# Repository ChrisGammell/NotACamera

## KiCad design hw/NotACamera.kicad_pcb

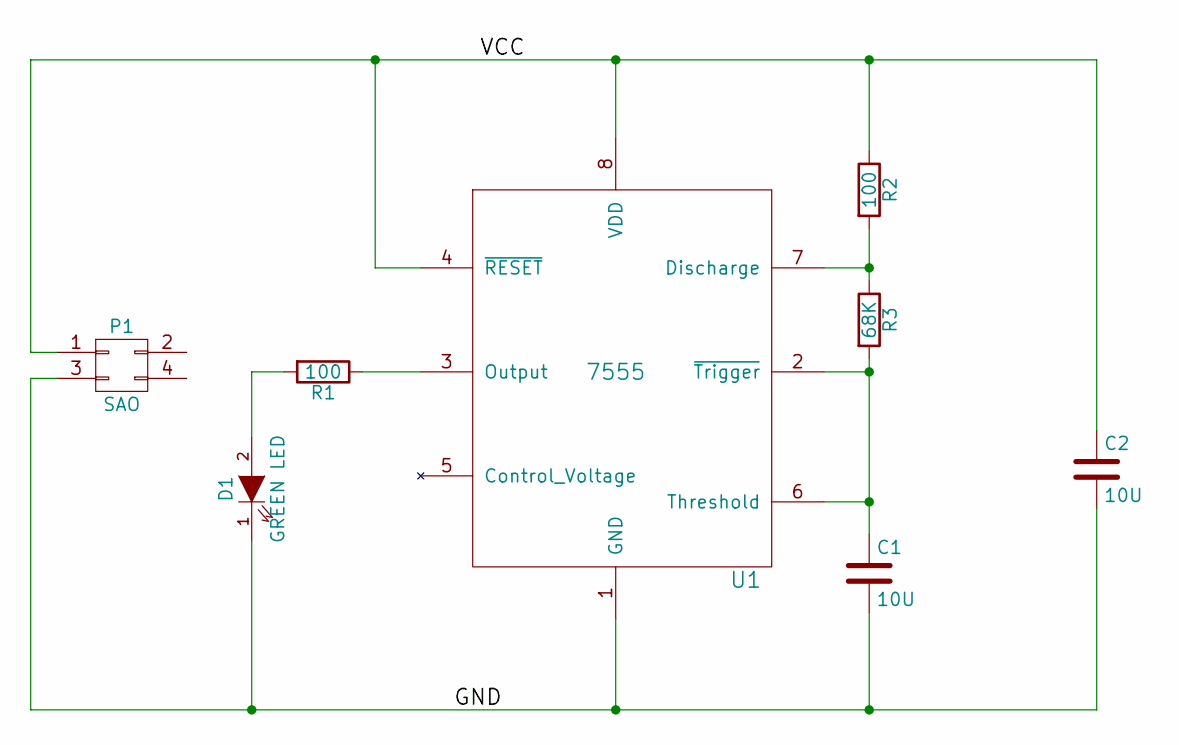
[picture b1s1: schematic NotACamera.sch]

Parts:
C1, C2: 10U; R_0805_HandSoldering; MPN MPN
D1: GREEN LED; R_0805_HandSoldering; MPN MPN
P1: SAO; Pin_Header_Straight_2x02
R1, R2: 100; R_0805_HandSoldering; MPN MPN
R3: 68K; R_0805_HandSoldering; MPN MPN
U1: 7555; SOIC-8-N

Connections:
/GND: C1.2, C2.2, D1.1 (K), P1.3, U1.1 (GND)
/VCC: C2.1, P1.1, R2.1, U1.4 (~RESET), U1.8 (VDD)
unnamed: C1.1, R3.2, U1.2 (~Trigger), U1.6 (Threshold)
unnamed: D1.2 (A), R1.2
unnamed: R1.1, U1.3 (Output)
unnamed: R2.2, R3.1, U1.7 (Discharge)

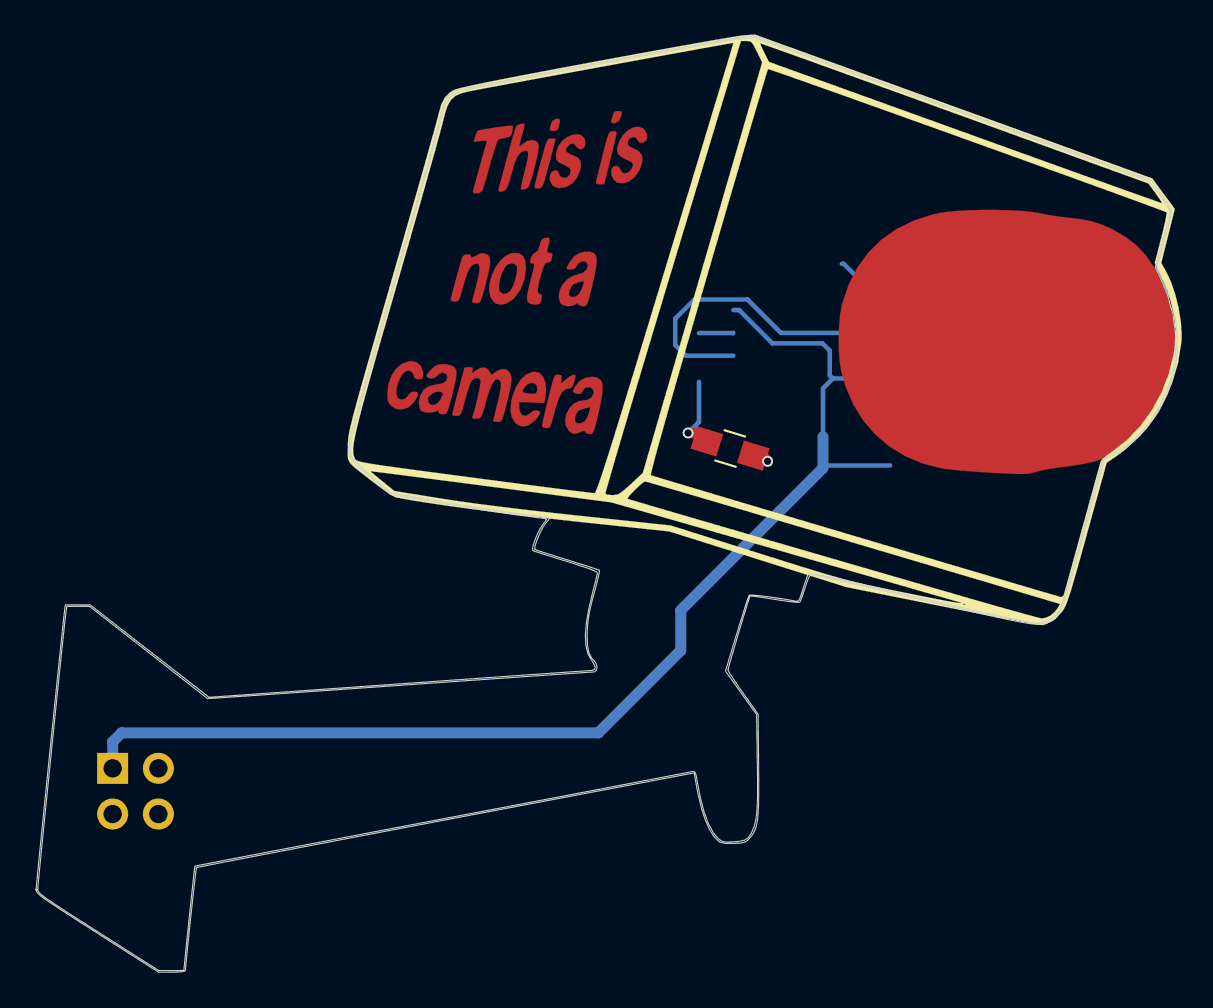
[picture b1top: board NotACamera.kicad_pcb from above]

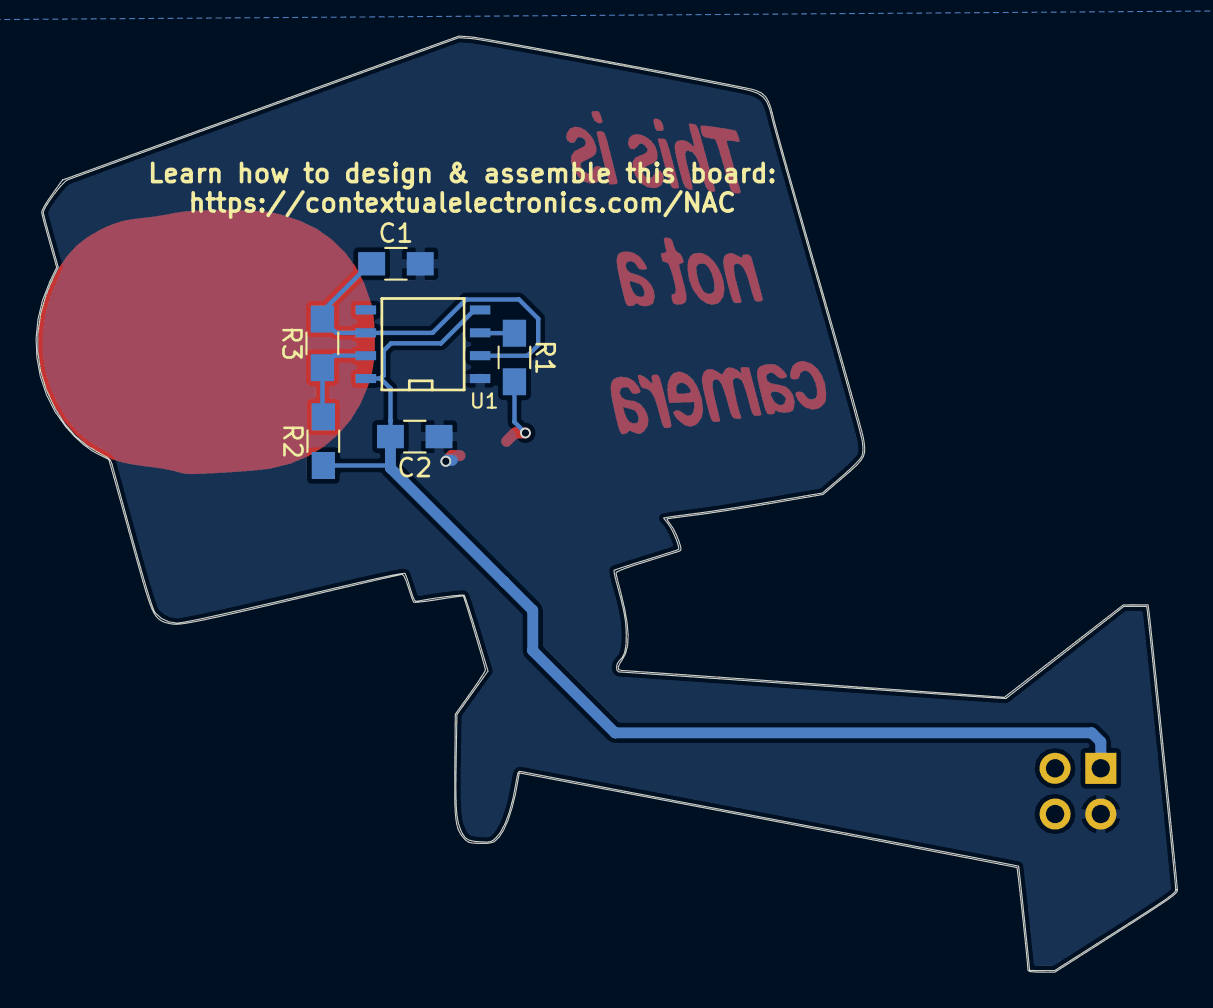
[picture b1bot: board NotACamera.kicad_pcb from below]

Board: 2 copper layers, 63.4 x 52.0 mm, 11 parts (6 on the bottom side), 6 nets.

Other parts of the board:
CU***: LOGO; NAC-CU
EC***: LOGO; NAC-OL
SM***: LOGO; NAC-SM-invert

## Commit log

2018-07-11 Split into directories
2018-07-11 Created initial graphics
2018-07-11 Updated copper image to have black on white coloration
2018-07-11 Finished initial layout
2018-07-11 Inverted copper layer on lens
2018-07-11 Implemented inverted lens
2018-07-11 Moved back silk refdes
2018-07-12 Finalized version of NAC
2018-07-12 Moved / modified back silkscreen
2018-07-12 Generated gerbers
2018-07-12 Final changes to gerbers
2018-07-30 Changed schematic for new connections, values and footprint associations
2018-07-31 Finished new layout, moving old gerbers
2018-07-31 Created v1 gerbers
2018-07-31 Tightened up some traces
